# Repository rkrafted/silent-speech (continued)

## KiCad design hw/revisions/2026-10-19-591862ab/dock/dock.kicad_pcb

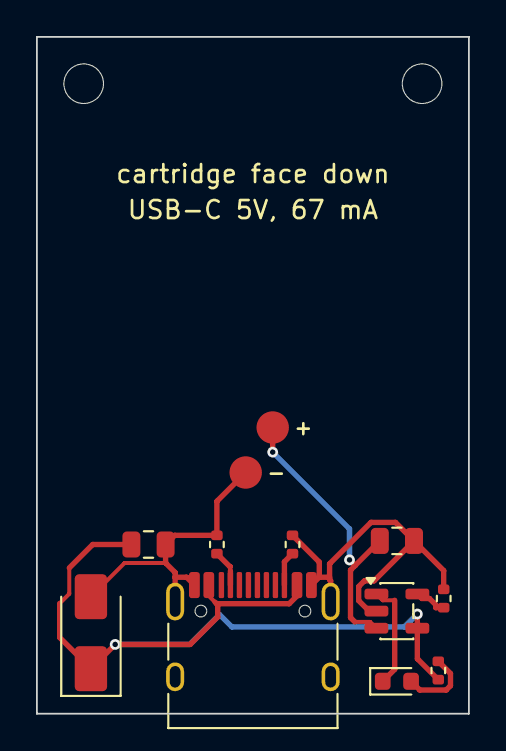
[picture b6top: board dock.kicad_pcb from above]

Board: 2 copper layers, 24.0 x 37.6 mm, 14 parts (0 on the bottom side), 8 nets.

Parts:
C1, C2: 10uF 25V; C_0805_2012Metric
D1: SMAJ5.0A; D_SMA
D2: LED red (charging); LED_0603_1608Metric
H1, H2: M2_NPTH_clamp
J1: TYPE-C-31-M-12; USB_C_Receptacle_HRO_TYPE-C-31-M-12
R1, R2: 5.1k; R_0402_1005Metric
R3: 15k; R_0402_1005Metric
R4: 1k; R_0402_1005Metric
TP1: BATT+ contact; TabPad_D1.8mm
TP2: BATT- contact; TabPad_D1.8mm
U1: MCP73831T-2ACI/OT; SOT-23-5

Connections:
CC1: J1.A5, R1.1
CC2: J1.B5, R2.1
GND: C1.2, C2.2, D1.2, J1.A1, J1.A12, J1.B1, J1.B12, J1.SH, R1.2, R2.2, R3.2, TP2.1, U1.2
LED_A: D2.2, R4.2
PROG: R3.1, U1.5
STAT: D2.1, U1.1
VBAT: C2.1, TP1.1, U1.3
VBUS: C1.1, D1.1, J1.A4, J1.A9, J1.B4, J1.B9, R4.1, U1.4

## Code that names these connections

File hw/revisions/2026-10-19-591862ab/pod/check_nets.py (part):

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    check(all(s == {"REF"} for s in inn), "IN1N..IN8N all on REF (referential montage)")
    check(pins_on("REF") - {p for p in pins_on("REF") if p[0] == "U1"} == {("R9", "2"), ("C9", "1")},
          "REF = 8x INxN + R9 (2.2k) + C9 (1nF) only")
    check(pins_on("REF_ELEC") == {("P9", "1"), ("FB9", "1"), ("D4", net_pin("D4", "IO1"))},
          "REF_ELEC = pogo P9 + ESD D4 + bead FB9")
    check(pins_on("REF_F") == {("FB9", "2"), ("R9", "1")}, "REF_F = FB9 -> R9 only")
    for i in range(1, 9):
        p = pins_on("IN%dP" % i)
        e = pins_on("E%d" % i)
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        check(net_of.get(("C%d" % i, "2")) == "GND", "C%d (input EMI cap) to GND" % i)

    # --- bias / RLD -----------------------------------------------------------------
    u1_rldout = {p for p in pins_on("RLDOUT") if p[0] == "U1"}
    check(func_net("U1", "RLDOUT") == {"RLDOUT"} and len(u1_rldout) == 1
          and pins_on("RLDOUT") - u1_rldout == {("R10", "1"), ("C11", "1"), ("R25", "1")},
          "RLDOUT = feedback R10/C11 + series R25 only (no capacitive load on the amp output)")
    check(pins_on("BIAS_F") == {("R25", "2"), ("C10", "1"), ("FB10", "2")}, "BIAS_F = R25 10k -> C10 1nF + bead FB10")
    check(pins_on("BIAS") == {("P10", "1"), ("FB10", "1"), ("D4", net_pin("D4", "IO2"))},
          "BIAS = pogo P10 + ESD D4 + bead FB10 (RLD reaches the body only through 10k)")
    check(func_net("U1", "RLDINV") == {"RLDINV"} and pins_on("RLDINV") - {p for p in pins_on("RLDINV") if p[0] == "U1"}
          == {("R10", "2"), ("C11", "2")}, "RLDINV = R10 392k || C11 10nF from RLDOUT only (TI SBAU171D 4.8)")
    check(len([1 for r, p, _ in nets.get("BIAS", set()) if r.startswith("P") and r[1:].isdigit()]) == 1, "exactly one bias electrode")

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        check(func_net("U1", f) == {"GND"}, "%s on GND" % f)
    for f in ("TESTP_PACE_OUT1", "TESTP_PACE_OUT2", "RLDIN"):
        check(func_net("U1", f) == {"+3.3VA"}, "%s on AVDD (TI pin table note 1: unused pins to AVDD)" % f)
    for f in ("GPIO1", "GPIO2", "GPIO3", "GPIO4"):
        check(func_net("U1", f) == {"GND"}, "%s shorted to DGND (TI: GPIOs are inputs, do not float)" % f)
    check(func_net("U1", "DVDD") == {"+3V3"}, "DVDD on +3V3 (LDO2)")
    # rev 0.7: CLKSEL on NINA pin 23 with a 100k pull-up (internal oscillator by default; low = slave pod)
    check(func_net("U1", "CLKSEL") == {"CLKSEL"} and net_of.get(("U2", "23")) == "CLKSEL"
          and net_of.get(("R33", "1")) == "+3V3" and net_of.get(("R33", "2")) == "CLKSEL"
          and pins_on("CLKSEL") == {("U1", [p for r, p, f in nets["CLKSEL"] if r == "U1"][0]), ("U2", "23"), ("R33", "2")},
          "CLKSEL = NINA pin 23, 100k pull-up (internal oscillator by default)")
    for f, net, caps in (("VREFP", "VREFP", {"C12", "C13"}), ("VCAP1", "VCAP1", {"C14"}), ("VCAP2", "VCAP2", {"C15"}),
                         ("VCAP3", "VCAP3", {"C16"}), ("VCAP4", "VCAP4", {"C17"}), ("WCT", "WCT", {"C33"}),
                         ("RLDREF", "RLDREF", {"C32"})):
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    check(net_of.get(("R21", "1")) == "+3V3" and net_of.get(("R21", "2")) == "CS_N", "CS pulled high at boot")
    check(net_of.get(("R22", "1")) == "START" and net_of.get(("R22", "2")) == "GND", "START pulled low at boot")
    check(net_of.get(("R23", "1")) == "+3V3" and net_of.get(("R23", "2")) == "ADS_RESET", "RESET pulled high at boot")
    check(func_net("U1", "CLK") == {"CLK_SYNC"} and ("TP1", "1") in pins_on("CLK_SYNC"), "CLK on test pad TP1")

    # --- radio supply, programming, 5 V safety ----------------------------------------
    check(net_of.get(("U2", "10")) == "+3V3" and net_of.get(("U2", "9")) == "+3V3", "NINA VCC and VCC_IO on +3V3")
    check(all(net_of.get(("U2", p)) == "GND" for p in ("6", "12", "14", "26", "30", "53", "56", "57")),
          "NINA GND pins + EGP + EAGP on GND")
    check(pins_on("VBUS_MOD") == {("U2", "31"), ("R34", "1")} and net_of.get(("R34", "2")) == "GND"
          and ("R34", "0R DNP") in values, "NINA VBUS open; R34 0R to GND not fitted (rev 0.7: no USB)")
    check("VBUS" not in nets, "no VBUS net on the pod (rev 0.7)")
    five_v = {"BAT_RAW", "+BATT"}
    check(not any(r == "U2" for n in five_v for r, _, _ in nets.get(n, set())),
          "no 3.3 V radio GPIO on a net that can exceed 3.6 V (VBUS, STAT, battery)")
    # Tag-Connect TC2030 ARM SWD pinout: 1 VCC, 2 SWDIO, 3 nRESET, 4 SWCLK, 5 GND, 6 SWO (open)
    check(net_of.get(("U2", "15")) == "SWDIO" and net_of.get(("J3", "2")) == "SWDIO", "SWDIO on J3.2")
    check(net_of.get(("U2", "11")) == "SWDCLK" and net_of.get(("J3", "4")) == "SWDCLK", "SWDCLK on J3.4")
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    check(("J3", "6") not in net_of or net_of[("J3", "6")].startswith("unconnected"), "J3.6 SWO open")

    # --- power path -------------------------------------------------------------------
    check(pins_on("BAT_RAW") == {("J2", "1"), ("Q2", "3"), ("TP15", "1")}, "battery + (plug or sled) -> AO3401A drain only")
    check(("TP16", "1") in pins_on("GND"), "battery sled - contact on GND")
    check(net_of.get(("Q2", "2")) == "+BATT" and net_of.get(("Q2", "1")) == "GND" and net_of.get(("J2", "2")) == "GND",
          "AO3401A source -> +BATT, gate -> GND (reverse-polarity protection)")
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    check(not allrefs & {"U5", "R11", "C28", "D5", "R16"}, "no charger parts on the pod (rev 0.7: dock charges)")
    check(("C29", "1") in pins_on("+BATT") and net_of.get(("C29", "2")) == "GND", "10 uF bulk on +BATT")
    # two-pod clock link: ADS CLK -> R31 100R -> P11, ESD on D4 IO3, 1M pull-down; P12 = GND
    check(pins_on("CLK_POGO") == {("R31", "2"), ("P11", "1"), ("D4", net_pin("D4", "IO3"))}
          and net_of.get(("R31", "1")) == "CLK_SYNC" and ("R31", "100R") in values,
          "pogo 11 = CLK_POGO <- 100R R31 <- ADS CLK, ESD on D4 IO3")
    check(net_of.get(("R32", "1")) == "CLK_SYNC" and net_of.get(("R32", "2")) == "GND" and ("R32", "1M") in values,
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    for u in ("U3", "U4"):
        check(func_net(u, "IN") == {"+BATT"} and func_net(u, "EN") == {"+BATT"} and func_net(u, "GND") == {"GND"},
              "%s: IN and EN on +BATT" % u)
    check(net_of.get(("R14", "1")) == "+BATT" and pins_on("BAT_SENSE") == {("R14", "2"), ("R15", "1"), ("C30", "1"),
                                                                           ("U2", "16")}
          and net_of.get(("R15", "2")) == "GND", "battery divider 1M/1M -> NINA pin 16 (P0.03/AIN1)")
    check(not any(r.startswith("LED") for ns in nets.values() for r, _, _ in ns), "no LEDs on the board (hidden wearable)")
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
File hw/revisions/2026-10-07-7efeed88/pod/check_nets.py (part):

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    check(all(s == {"REF"} for s in inn), "IN1N..IN8N all on REF (referential montage)")
    check(pins_on("REF") - {p for p in pins_on("REF") if p[0] == "U1"} == {("R9", "2"), ("C9", "1")},
          "REF = 8x INxN + R9 (2.2k) + C9 (1nF) only")
    check(pins_on("REF_ELEC") == {("P9", "1"), ("R9", "1"), ("D4", net_pin("D4", "IO1"))},
          "REF_ELEC = pogo P9 + R9 + ESD D4")
    for i in range(1, 9):
        p = pins_on("IN%dP" % i)
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        check(net_of.get(("C%d" % i, "2")) == "GND", "C%d (input EMI cap) to GND" % i)

    # --- bias / RLD -----------------------------------------------------------------
    check(func_net("U1", "RLDOUT") == {"BIAS"} and pins_on("BIAS") >= {("P10", "1"), ("R10", "1"), ("C11", "1"),
                                                                       ("C10", "1")},
          "RLDOUT -> BIAS pogo 10, with R10/C11 feedback and C10")
    check(func_net("U1", "RLDINV") == {"RLDINV"} and pins_on("RLDINV") - {p for p in pins_on("RLDINV") if p[0] == "U1"}
          == {("R10", "2"), ("C11", "2")}, "RLDINV = R10 392k || C11 10nF from BIAS only (TI SBAU171D 4.8)")
    check(len([1 for r, p, _ in nets.get("BIAS", set()) if r.startswith("P") and r[1:].isdigit()]) == 1, "exactly one bias electrode")

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        check(func_net("U1", f) == {"GND"}, "%s on GND" % f)
    for f in ("TESTP_PACE_OUT1", "TESTP_PACE_OUT2", "RLDIN"):
        check(func_net("U1", f) == {"+3.3VA"}, "%s on AVDD (TI pin table note 1: unused pins to AVDD)" % f)
    for f in ("GPIO1", "GPIO2", "GPIO3", "GPIO4"):
        check(func_net("U1", f) == {"GND"}, "%s shorted to DGND (TI: GPIOs are inputs, do not float)" % f)
    check(func_net("U1", "DVDD") == {"+3V3"}, "DVDD on +3V3 (LDO2)")
    check(func_net("U1", "CLKSEL") == {"+3V3"}, "CLKSEL high = internal oscillator")
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    check(net_of.get(("R21", "1")) == "+3V3" and net_of.get(("R21", "2")) == "CS_N", "CS pulled high at boot")
    check(net_of.get(("R22", "1")) == "START" and net_of.get(("R22", "2")) == "GND", "START pulled low at boot")
    check(net_of.get(("R23", "1")) == "+3V3" and net_of.get(("R23", "2")) == "ADS_RESET", "RESET pulled high at boot")
    check(func_net("U1", "CLK") == {"CLK_SYNC"} and ("TP1", "1") in pins_on("CLK_SYNC"), "CLK on test pad TP1")

    # --- radio supply, programming, 5 V safety ----------------------------------------
    check(net_of.get(("U2", "10")) == "+3V3" and net_of.get(("U2", "9")) == "+3V3", "NINA VCC and VCC_IO on +3V3")
    check(all(net_of.get(("U2", p)) == "GND" for p in ("6", "12", "14", "26", "30", "53", "56", "57")),
          "NINA GND pins + EGP + EAGP on GND")
    check(pins_on("VBUS_MOD") == {("U2", "31"), ("R16", "2")} and net_of.get(("R16", "1")) == "VBUS",
          "NINA VBUS (5 V input) <- R16 2.2k <- VBUS")
    five_v = {"VBUS", "BAT_RAW", "+BATT"}
    check(not any(r == "U2" for n in five_v for r, _, _ in nets.get(n, set())),
          "no 3.3 V radio GPIO on a net that can exceed 3.6 V (VBUS, STAT, battery)")
    check(net_of.get(("U2", "15")) == "SWDIO" and ("TP3", "1") in pins_on("SWDIO"), "SWDIO on TP3")
    check(net_of.get(("U2", "11")) == "SWDCLK" and ("TP4", "1") in pins_on("SWDCLK"), "SWDCLK on TP4")
    check(net_of.get(("U2", "19")) == "MOD_RESET" and ("TP5", "1") in pins_on("MOD_RESET")
          and net_of.get(("R13", "1")) == "+3V3", "RESET_N on TP5 with R13 pull-up")

    # --- power path -------------------------------------------------------------------
    check(pins_on("BAT_RAW") == {("J2", "1"), ("Q2", "3")}, "battery + -> AO3401A drain only")
    check(net_of.get(("Q2", "2")) == "+BATT" and net_of.get(("Q2", "1")) == "GND" and net_of.get(("J2", "2")) == "GND",
          "AO3401A source -> +BATT, gate -> GND (reverse-polarity protection)")
    check(func_net("U5", "V_{DD}") == {"VBUS"} and func_net("U5", "V_{BAT}") == {"+BATT"}
          and func_net("U5", "V_{SS}") == {"GND"}, "MCP73831: VDD=VBUS, VBAT=+BATT, VSS=GND")
    check(func_net("U5", "PROG") == {"PROG"} and pins_on("PROG") - {("U5", "5")} == {("R11", "1")}
          and net_of.get(("R11", "2")) == "GND", "PROG = R11 10k to GND (100 mA)")
    check(not any(r == "U5" and f.upper() == "STAT" for ns in nets.values() if len(ns) > 1 for r, p, f in ns),
          "MCP73831 STAT left open (5 V-swinging output, no LED, no GPIO)")
    check(("C28", "1") in pins_on("VBUS") and ("C29", "1") in pins_on("+BATT"), "10 uF on VBUS and on VBAT")
    check(net_of.get(("D5", "1")) == "VBUS" and net_of.get(("D5", "2")) == "GND", "TVS cathode on VBUS, anode GND")
    check(("P11", "1") in pins_on("VBUS") and net_of.get(("P12", "1")) == "GND", "pogo 11 = VBUS, 12 = GND (adjacent: charger tab)")
    for u in ("U3", "U4"):
        check(func_net(u, "IN") == {"+BATT"} and func_net(u, "EN") == {"+BATT"} and func_net(u, "GND") == {"GND"},
              "%s: IN and EN on +BATT" % u)
    check(net_of.get(("R14", "1")) == "+BATT" and pins_on("BAT_SENSE") == {("R14", "2"), ("R15", "1"), ("C30", "1"),
                                                                           ("U2", "16")}
          and net_of.get(("R15", "2")) == "GND", "battery divider 1M/1M -> NINA pin 16 (P0.03/AIN1)")
    check(not any(r.startswith("LED") for ns in nets.values() for r, _, _ in ns), "no LEDs on the board (hidden wearable)")
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
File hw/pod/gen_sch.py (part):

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    elif n == "DVDD":
        ads[num] = "+3V3"
    elif n == "CLKSEL":
        ads[num] = "CLKSEL"                  # rev 0.7: NINA GPIO, 100k pull-up = internal oscillator by default
    elif n.startswith("GPIO"):
        ads[num] = "GND"                     # TI: GPIOs are inputs after reset, "short these pins to DGND"
    elif n == "NC":
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
# ================================================================ 4. radio
frame("4. Radio: u-blox NINA-B306-00B (nRF52840, internal antenna, 32.768 kHz crystal inside)", 480, 15, 760, 300,
      "ADS link on the outer left pin column (pins 1-5, 7, 8) + pin 25: none near the radio (UBX-17052099). EXP1-5 ARE near the radio: < 10 kHz only.")
nina = {num: None for num in PINS["pod:NINA-B306"]}
nina.update({"51": "QSPI_CS", "52": "QSPI_CLK", "50": "QSPI_IO0", "48": "QSPI_IO1", "49": "QSPI_IO2",
             "47": "QSPI_IO3", "17": "EXP1", "18": "EXP2", "20": "EXP3", "21": "EXP4", "22": "EXP5",
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
# ================================================================ 7. flash + expansion
frame("7. 16 MB flash (record without a phone) + expansion pads (open hardware: add sensors later)", 480, 410, 760, 530,
      "W25Q128JV on the nRF52840 QSPI pins (u-blox recommended QSPI pins). EXP1-3: spare GPIOs (I2C/SPI/UART/PWM; analog). EXP4/EXP5 = I2C SDA/SCL (fuel gauge bus, add sensors on it).")
place("U6", "Memory_Flash:W25Q128JVP", "W25Q128JVPIQ (16 MB)", 540, 470,
      {"1": "QSPI_CS", "2": "QSPI_IO1", "3": "QSPI_IO2", "4": "GND", "5": "QSPI_IO0", "6": "QSPI_CLK",
       "7": "QSPI_IO3", "8": "+3V3", "9": "GND"},
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head = ['(kicad_sch (version 20250114) (generator "eeschema") (generator_version "9.0")',
        '(uuid "%s")' % ROOT, '(paper "A1")',
        '(title_block (title "ss-pod v1: ADS1298 + nRF52840 (NINA-B306) EMG pod") (rev "0.7") '
        '(company "ss-pod") (comment 1 "Rev 0.7: no charger, MAX17048, CLKSEL GPIO + CLK on P11; rev 0.6: cartridge pads TP15/TP16; rev 0.4: ADS link on NINA outer pins; rev 0.3: BIAS 10k, ferrites") '
        '(comment 2 "Analog front end: TI SBAS459K + ADS1298ECG-FE (SBAU171D) + OpenBCI Cyton (CC BY-SA 4.0)"))',
        '(lib_symbols']
used = sorted({p[1] for p in parts} | set(POWER.values()) | {"power:PWR_FLAG"})
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
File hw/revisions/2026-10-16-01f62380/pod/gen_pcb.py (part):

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u1.SetOrientationDegrees(best[1])

# filter rows (bottom, under the pogo grid): ESD -> bead -> 2.2k -> 1nF -> ADS. Rows follow the
# ADS input order; REF at the end nearest the REF pins' middle, BIAS at the RLD end.
lines = []
for i in range(1, 9):
    lines.append((pad_xy("U1", {1: 16, 2: 14, 3: 12, 4: 10, 5: 8, 6: 6, 7: 4, 8: 2}[i])[1],
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decap("C20", 50, out=2.05, along=1.1 * sgd)   # DVDD pin 48 (corner; right side has no room)
# bulk caps (0805) in a second row above the 0402 decaps, clear of the antenna keep-out (y < 103.4).
# Pad 1 sits exactly in line with a free gap so its pre-route runs straight to the pin:
# C14 (VCAP1) pad 1 above pin 28 (no 0402 there); C13 (VREFP) pad 1 above pin 25, between C12 and C17.
p25, p28 = pad_xy("U1", 25), pad_xy("U1", 28)
put("C13", p25[0] - 1.0 * sgb, 104.3, side="B", toward=(p25[0], 110), axis="h")   # VREFP 10u
put("C14", p28[0] + 1.0 * sgb, 104.3, side="B", toward=(p28[0], 110), axis="h")   # VCAP1 22u
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    (x1, y1), (x3, y3) = pad_xy(ldo, 1), pad_xy(ldo, 3)
    o = -1 if x1 < pcbnew.ToMM(placed[ldo].GetPosition().x) else 1
    lock_path([(x1, y1), (x1 + o * 0.95, y1), (x3 + o * 0.95, y3), (x3, y3)], "+BATT", pcbnew.B_Cu, 0.25)
# ADS1298 CLKSEL (pin 52, +3V3) joins the pin-50 DVDD decoupling track just outside the pin row
p50, p52 = pad_xy("U1", 50), pad_xy("U1", 52)
oy = 1 if p50[1] > ADS[1] else -1
tip = p50[1] + oy * 0.74
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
